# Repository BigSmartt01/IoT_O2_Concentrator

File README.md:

# IoT Oxygen Concentrator Integration

**Purity Monitoring, Alert System and Compressor Control**

A non-invasive integration module for PSA oxygen concentrators. The system monitors
oxygen purity on the outlet line, escalates alerts through five tiers as purity drops,
notifies a caregiver via SMS or voice call, and cuts compressor power only at true
system failure levels.

---

## What This System Does

| Feature | Description |
|---|---|
| Purity monitoring | OCS-3FL2.0 ultrasonic sensor on post-filtration outlet (UART2) |
| Local display | LCD 2004 (I2C) shows O2%, flow, temperature, status, GSM signal, uptime |
| Five-tier alerts | NORMAL → WARNING → DANGER → SEVERE → CRITICAL, each with distinct buzzer pattern and response |
| Caregiver config | Number stored in NVS flash — configurable via USB serial, SMS command, **or the web portal** |
| Three input modes | Potentiometer (demo), WiFi captive portal (demo sliders), or real Sensor (UART) |
| Boot illusion | On boot, simulates a sensor warm-up ramp until a real sensor is connected — no hardware required to demo |
| Fail-safe relay | Compressor only cuts at CRITICAL (near-ambient O2, sustained) — every other tier keeps it running while alerting |

The concentrator itself is **not modified**. All integration is external in a separate enclosure.

---

## Hardware

| Component | Role |
|---|---|
| ESP32 DevKit (standard) | Main microcontroller, 3 UARTs, WiFi AP for captive portal |
| OCS-3FL2.0 sensor | Oxygen purity, flow, temperature (UART2, 12-byte packet) |
| SIM800L GSM EVB | SMS and voice call via Nigerian GSM network (UART1) |
| LCD 2004 + I2C backpack | Local display, 4 rows |
| 5V relay module + NPN driver (BC337) | Compressor power control, active-HIGH from GPIO |
| Active buzzer (5V) | Audible alert, pattern varies by tier |
| LM2596 buck converter | 12V to 5V regulated rail |
| 12V AC-DC module | Mains AC to 12V DC from concentrator supply |
| 2200uF electrolytic caps (x3) | Bulk capacitance on 5V rail, 12V rail, and SIM800L supply |
| Potentiometer 10k | Demo sensor substitute (ADC, GPIO 34) |

Full wiring, schematic, and PCB layout are documented in `docs/`.

---

## Project Structure

```
project-root/
├── firmware/               # Arduino sketch (.ino), config.h, portal_html.h
├── hardware/                # KiCad schematic, PCB layout, Gerber files
├── docs/                    # Full project documentation, diagrams, images
├── README.md                # This file
├── SETUP.md                 # Step-by-step setup guide for Arduino IDE
└── .gitignore
```

---

## Alert Tiers

The system escalates through five tiers based on O2 purity. Only the DANGER tier
and above place a voice call; only WARNING sends SMS. **The compressor keeps running
through every tier except CRITICAL** — the design assumes a caregiver may not respond
immediately, so oxygen delivery is only stopped once purity has effectively fallen to
ambient air levels, at which point the compressor was providing no therapeutic value anyway.

| Tier | O2 Purity | Buzzer | Caregiver Contact | Relay |
|---|---|---|---|---|
| NORMAL | ≥ 85% | Silent | — | ON |
| WARNING | 70% – 85% | Single beep, 1s cycle | SMS | ON |
| DANGER | 35% – 70% | Double beep, 1s cycle | Voice call | ON |
| SEVERE | 23% – 35% | Continuous tone | Voice call | ON |
| CRITICAL | < 23% (3 consecutive readings) | Continuous tone | Voice call | **OFF** |

Thresholds are runtime-adjustable (see [Configuration](#configuration-thresholds-and-caregiver-number) below)
and persist in NVS flash. Default fallback values live in `firmware/config.h`.

All alerts are suppressed for **30 seconds after boot** to allow the sensor warm-up
and GSM network registration to settle before any buzzer, SMS, or call can fire.

---

## Input Modes

The system supports three interchangeable data sources, switchable at any time from
the web portal without reflashing:

- **Potentiometer** — a physical demo knob on GPIO 34, mapped to 21%–95.6%
- **WiFi** — connect to the device's own captive portal and drag sliders for O2, flow, and temperature
- **Sensor** *(boots here by default)* — real UART2 data from the OCS-3FL2.0. If no real sensor is connected, the system runs a realistic warm-up illusion (ramping 21% → ~92% over ~15 seconds, then settling with slight jitter) so the full alert chain can be demonstrated with no hardware attached. The moment a real sensor sends valid packets, live data takes over automatically.

<p align="center">
  <br>
  <em>WiFi captive portal for demo input and caregiver configuration</em>
</p>

---

## Firmware Architecture

The firmware uses **FreeRTOS** (built into the ESP32 Arduino core — no extra install needed).
Five tasks run concurrently, sharing data through two mutex-protected resources:

| Task | Core | Responsibility |
|---|---|---|
| `sensorTask` | 0 | Reads active input mode (pot / WiFi / sensor), updates shared O2 data |
| `displayTask` | 0 | Updates all 4 rows of the LCD every 500 ms |
| `webTask` | 0 | Hosts the WiFi AP, captive portal, and DNS redirect |
| `gsmTask` | 1 | Initialises modem on boot, monitors network registration every 5s |
| `configTask` | 1 | Handles USB serial and incoming SMS configuration commands |
| `alertTask` | 1 (highest priority) | Evaluates the 5-tier state machine, drives buzzer/relay/SMS/call |

`dataMutex` protects the shared sensor reading; `modemMutex` protects all TinyGSM AT command calls,
since multiple tasks share the same SIM800L UART.

---

## Quick Start

See [`SETUP.md`](SETUP.md) for the full step-by-step setup guide.

1. Install Arduino IDE 2.x
2. Add ESP32 board support
3. Install required libraries (listed in SETUP.md — includes ESPAsyncWebServer for the portal)
4. Open `firmware/IoT_O2_Concentrator.ino`
5. Set board to **ESP32 Dev Module**, select your COM port
6. Upload

---

## Configuration: Thresholds and Caregiver Number

Three interchangeable ways to configure the system — all write to the same NVS storage:

**1. Web portal (easiest, works in any input mode)**
Connect to WiFi network `O2-Controller` (password `12345678`), a captive portal should
open automatically. Enter the caregiver number in the "Caregiver Number" card and tap **Set**.

**2. USB Serial** (115200 baud)
```
SET NUM +2348012345678
SET WARN 72
SET NORM 87
STATUS
HELP
```

**3. SMS to the device SIM**
Send the same commands as SMS text to the SIM card installed in the SIM800L EVB.
The device replies with confirmation and deletes the processed message.

<p align="center">
  <br>
  <em>Caregiver receiving a live SMS alert</em>
</p>

All three methods are always available regardless of which input mode (pot/WiFi/sensor) is active.

---

## Documentation

Full design documentation is in the `docs/` folder. It covers:
- System architecture and power design
- Sensor UART protocol and 12-byte packet parsing
- Relay driver circuit (NPN, active-HIGH from GPIO)
- Five-tier alert logic and state machine
- KiCad schematic and PCB layout
- Wiring connection reference table
- Bill of Materials

---

*Project by Smart Ayodele.*
*README last updated to match firmware Rev 1.4*

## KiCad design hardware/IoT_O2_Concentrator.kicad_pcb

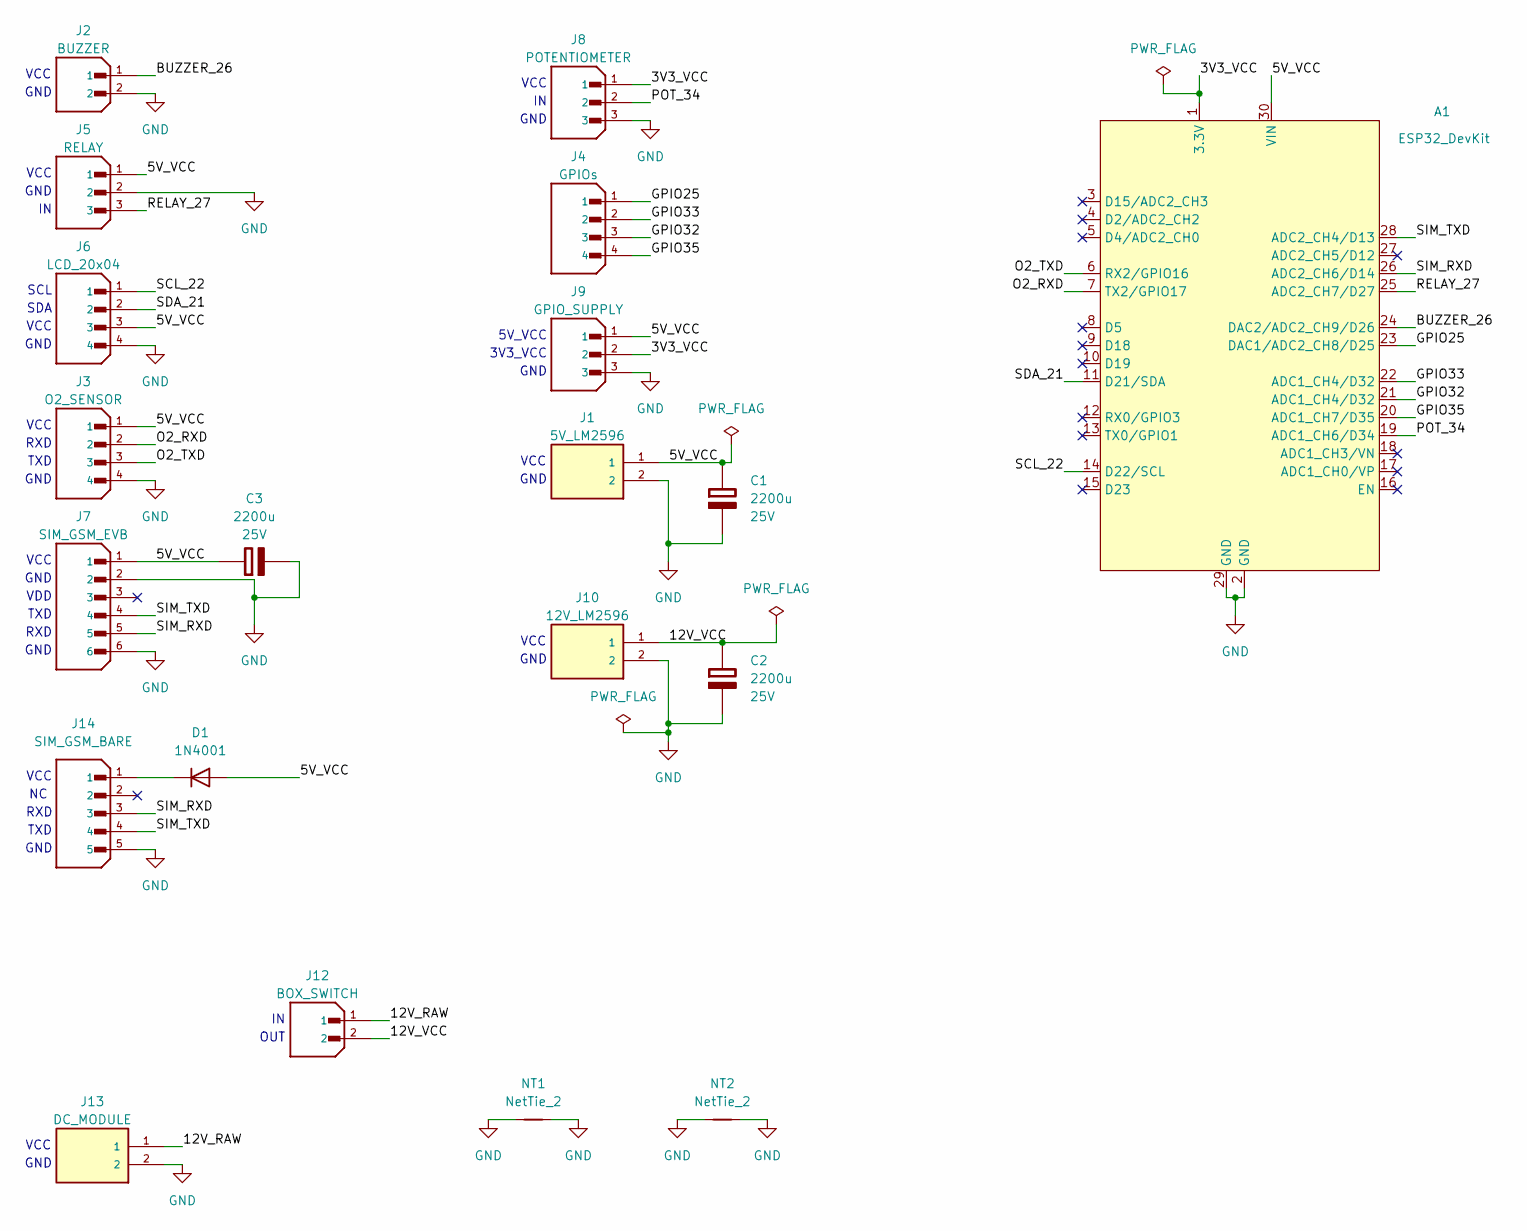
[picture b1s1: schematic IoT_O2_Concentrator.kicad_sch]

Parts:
A1: ESP32_DevKit; DOIT_ESP32_DEVKIT_30Pins
C1, C2, C3: 2200u; C_Radial_D10.0mm_H12.5mm_P5.00mm; Rating 25V
D1: 1N4001; D_DO-41_SOD81_P10.16mm_Horizontal
J1: 5V_LM2596; TB002-500-02BE
J2: BUZZER; JST_B2B-XH-A; PARTREV N/A
J3: O2_SENSOR; JST_B4B-XH-A; PARTREV 7/4/21
J4: GPIOs; JST_B4B-XH-A; PARTREV 7/4/21
J5: RELAY; JST_B3B-XH-A; PARTREV 7/4/21
J6: LCD_20x04; JST_B4B-XH-A; PARTREV 7/4/21
J7: SIM_GSM_EVB; JST_B6B-XH-A; PARTREV 7/4/21
J8: POTENTIOMETER; JST_B3B-XH-A; PARTREV 7/4/21
J9: GPIO_SUPPLY; JST_B3B-XH-A; PARTREV 7/4/21
J10: 12V_LM2596; TB002-500-02BE
J12: BOX_SWITCH; JST_B2B-XH-A; PARTREV N/A
J13: DC_MODULE; TB002-500-02BE
J14: SIM_GSM_BARE; JST_B5B-XH-A; PARTREV 7/4/21
NT1, NT2: NetTie_2; JUP_P10mm

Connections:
/3V3_VCC: A1.1 (3.3V), J8.1, J9.2
/5V_VCC: A1.30 (VIN), C1.1 (+), C3.1 (+), D1.2 (A), J1.1, J3.1, J5.1, J6.3, J7.1, J9.1
/12V_RAW: J12.1, J13.1
/12V_VCC: C2.1 (+), J10.1, J12.2
/BUZZER_26: A1.24 (DAC2/ADC2_CH9/D26), J2.1
/GPIO25: A1.23 (DAC1/ADC2_CH8/D25), J4.1
/GPIO32: A1.21 (ADC1_CH4/D32), J4.3
/GPIO33: A1.22 (ADC1_CH4/D32), J4.2
/GPIO35: A1.20 (ADC1_CH7/D35), J4.4
/O2_RXD: A1.7 (TX2/GPIO17), J3.2
/O2_TXD: A1.6 (RX2/GPIO16), J3.3
/POT_34: A1.19 (ADC1_CH6/D34), J8.2
/RELAY_27: A1.25 (ADC2_CH7/D27), J5.3
/SCL_22: A1.14 (D22/SCL), J6.1
/SDA_21: A1.11 (D21/SDA), J6.2
/SIM_RXD: A1.26 (ADC2_CH6/D14), J7.5, J14.3
/SIM_TXD: A1.28 (ADC2_CH4/D13), J7.4, J14.4
GND: A1.2 (GND), A1.29 (GND), C1.2 (-), C2.2 (-), C3.2 (-), J1.2, J2.2, J3.4, J5.2, J6.4, J7.2, J7.6, J8.3, J9.3, J10.2, J13.2, J14.5, NT1.1, NT1.2, NT2.1, NT2.2
unnamed: D1.1 (K), J14.1

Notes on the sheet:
GND
VCC
TXD
RXD
SCL
SDA
3V3_VCC
5V_VCC
OUT
VDD

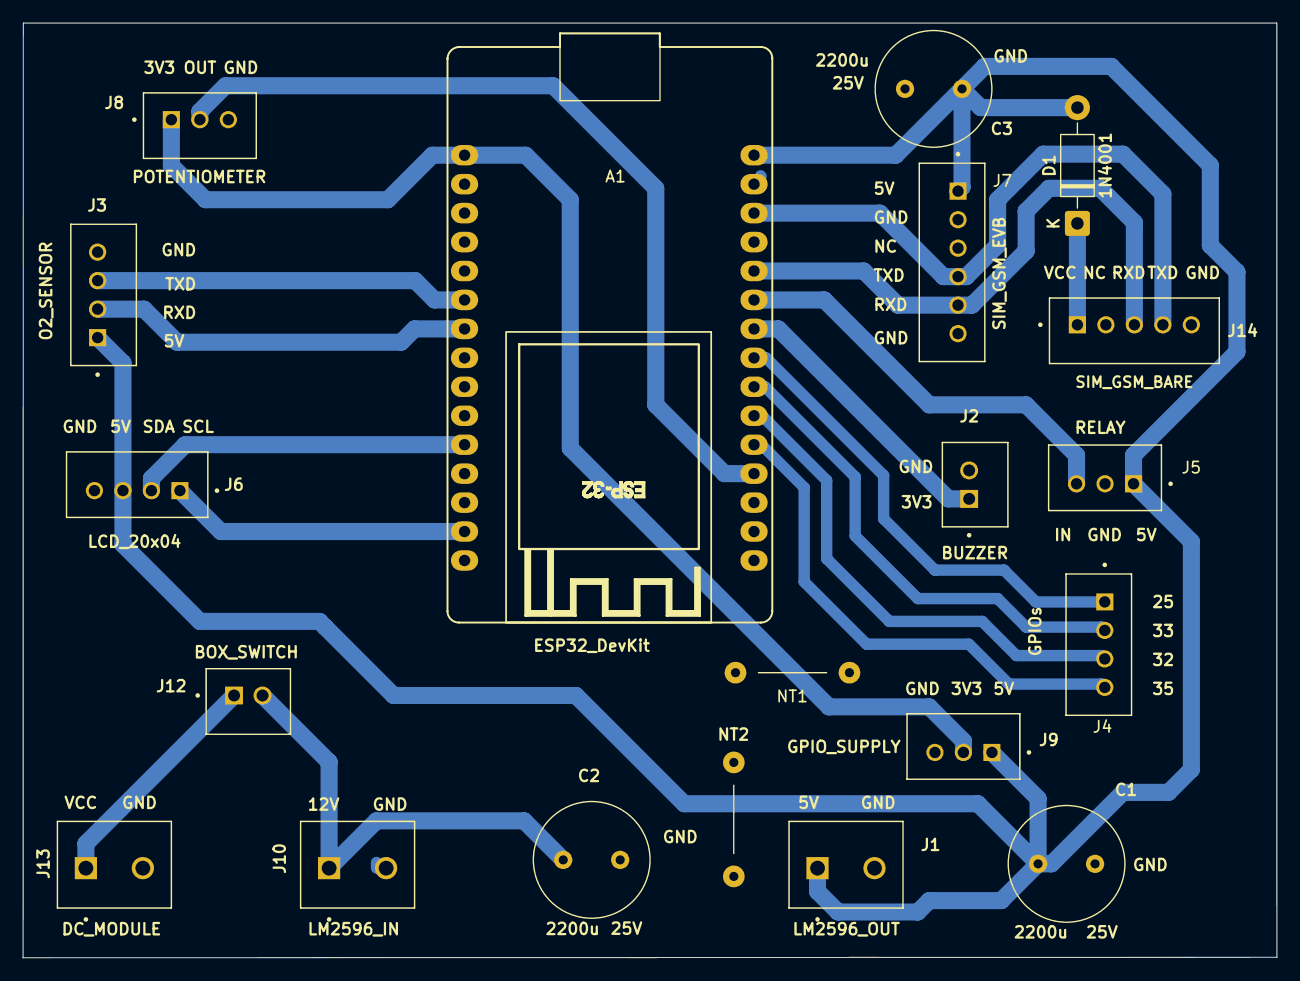
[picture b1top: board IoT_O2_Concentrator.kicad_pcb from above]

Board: 2 copper layers, 110.0 x 82.0 mm, 20 parts (0 on the bottom side), 19 nets.

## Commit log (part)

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2026-06-23 First Push with V1.2 documentation
2026-06-23 Start of Kicad Schematic
2026-06-23 Snapping to grid errors
2026-06-24 Started PCB routing
2026-06-24 Finishing the routing
2026-06-24 Routing with correct SIM tx/rx & labelling
2026-06-25 PCB Routing completed
2026-06-26 Corrected the firmware and added the O2 data derivation
2026-06-26 Added SMS polling and NVS
2026-06-26 DOCX v1.3 added
2026-06-27 Project firmware and documentation completed
